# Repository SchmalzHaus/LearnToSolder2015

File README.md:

# LearnToSolder2015
Learn-To-Solder kit, Hopinks 4th grade, 2015

This is a very simple kit to practice your soldering on.

It was developed by Deanna Schmalz (deanna@schmalzhaus.com) for the 4th grade class at Glen Lake Elementary School in 2015.

The Bill Of Materials (BOM) is as follows (to make 100 kits):

(from E-bay)

* 1 100pcs 5mm White Self Flash Flashing Blink Water Clear Bright LED Light #3644
* 1 100pcs 5mm blue Self Flash Flashing Blink Water Clear Bright LED Light #4435
* 2 50Pcs SS12D00G3 2 Position SPDT 1P2T 3 Pin PCB Panel Mini Vertical Slide Switch
* 1 Sony CR2032 3V Lithium Coin Battery (100 Coin Cells)
* 1 100 pcs CR2025 CR2032 Computer Coin Button Cell Battery Box Socket Holder Case

(from BatchPCB)
* 100 boards from the gerbers

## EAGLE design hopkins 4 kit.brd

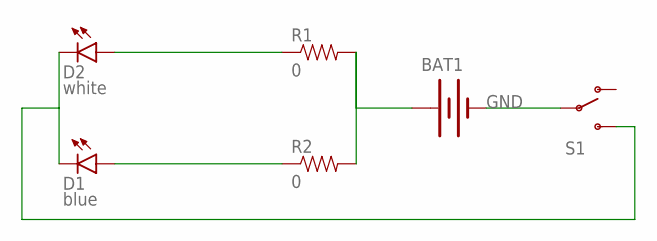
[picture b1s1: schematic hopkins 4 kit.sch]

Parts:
BAT1: BATTERY20PTH; BATTCOM_20MM_PTH
D1: blue; LED5MM
D2: white; LED5MM
R1, R2: 0; AXIAL-0.4
S1: SWITCH-SPDTPTH_LOCK; SWITCH-SPDT_LOCK.007S

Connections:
GND: BAT1.2 (-), S1.2
unnamed: BAT1.1 (+), R1.P$2 (2), R2.P$2 (2)
unnamed: D2.A, R1.P$1 (1)
unnamed: D1.A, R2.P$1 (1)
unnamed: D1.K (C), D2.K (C), S1.3 (S)

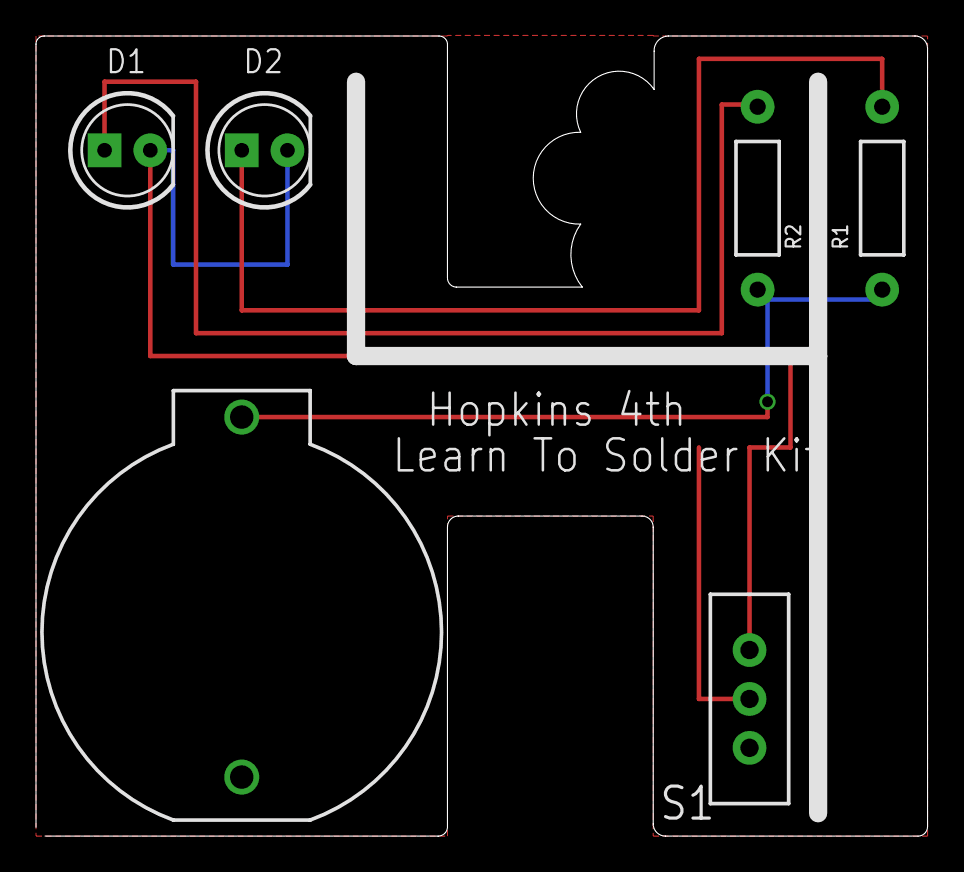
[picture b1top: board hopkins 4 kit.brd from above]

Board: 2 copper layers, 49.5 x 44.5 mm, 6 parts (0 on the bottom side), 5 nets.

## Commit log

2015-05-29 Checking in files for the first time.
2015-05-29 Updated readme.md.
2015-06-01 Added Power Point presentation given at Maker Faire MSP 2015.
2018-03-18 Create LICENSE

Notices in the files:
parts and their libraries:
SparkFun-Electromechanical: Licensing: Creative Commons ShareAlike 4.0 International - https://creativecommons.org/licenses/by-sa/4.0
